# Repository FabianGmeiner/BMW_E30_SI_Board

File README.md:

# About this Project

I'm currently working on a little project for all the early model E30 drivers with SI board trouble from leaky batteries or mechanical damage.

I am reverse engineering the early model SI board, in my case the VDO version (VDO and motometer are interchangeable)

This initial version is a 1:1 copy of the original design. The main microcontroller, the crystal oscillator and the large pin header need to be desoldered and taken over to the new board, but all other components are readily available and stocked parts.

This is mainly to understand the schematics and the workings of the circuit. In a second step I will design my own board with a modern microcontroller and non-volatile storage to work without batteries, with modern and way cheaper components (similar to the board offered by  [ProgRama](https://www.programainc.com/item_detail.aspx?idproduct=177&idcategory=49&sf=)). Also playing with the idea of integrating further functionality, like configurable shift lights on the little indicator board, as all the necessary signals are there anyway.

Warm regards from Germany!

## Current Status

2024/06/24 I received the initial batch of PCBs for testing. This includes the main SI boards as well as the pre-facelift LED board (9 LEDs).

I got all the necessary components from either Mouser or Reichelt (german vendor), but everything is available at Mouser. The [BOM](https://github.com/FabianGmeiner/BMW_E30_SI_Board/blob/main/BOM_SI_Board_Reman.xlsx "BOM_SI_Board_Reman.xlsx") contains all the part descriptions as well as relevant part numbers and the component identification and placement on the second sheet.

The facelift indicator boards (7 LEDs, 3 Bulbs) is based on photographs only, as such I could not yet verify the dimensions apart from measurements from images. 
If anybody has one of those boards laying around and could provide peasurements that would be highly appreciated.

### Testing status

#### Main SI board
**2024/06/24** first board assembled ready for testing.    
**2024/06/30** first functional tests successful. All functions operate as they should, and current consumption is in a nominal range. I am currently building a little pulse generator to test the speed and rpm inputs and test if the oil service lights count down as expected. This will be combined with a long test with the board powered up to check the current consumption and temperatures over longer time. 

| **Test Description**                 | **Current Draw Board** | **Battery Current** | **Further Comments**                                    |
|--------------------------------------|------------------------|---------------------|---------------------------------------------------------|
| Initial Connection, T30 off, T15 off |                        | 9.2 µA              | Battery current measured between BAT_EN jumper          |
| T30 on, T15 off                      | 3.6 mA                 | 5.7 µA              | All lights stay off, battery current reduces.           |
| T30 on, T15 on                       | 145.9 mA               | 5.7 µA              | 5 green LEDs turn on, Inspection light turns on         |
| Activating T50 (starter signal)      |                        |                     | Relay clicks, pad indicator lights up                   |
| Releasing T50 (starter signal)       |                        |                     | Relay clicks, pad indicator turns off, LEDs turn off    |
| Reset Button Pressed                 | 30.4 mA                |                     | INSP light goes out after ~10s, all lights off          |
| T30 on, T15 off                      | 3.6 mA                 |                     | turning ignition off after reset                        |
| T30 on, T15 on                       | 89.4 mA                |                     | ignition back on, 5 green LEDs on, INSP light stays off |
| Activating and releasing T50         | 30.5 mA                |                     | Relay cycles, LEDs turn off. All lights off.            |
| T30 off, T15 off                     |                        | 9.2 µA              |                                                         |
| Battery charging current             |                        | 22.8 mA             | Battery charging with T15 on                            |
| Battery charging cutoff voltage      |                        |                     | Board stops charging at a cell voltage of 1.35 V        |

The overall functionality, the current consumption as well as the charging current and voltage for the NiMh cells is within the expected range. 

#### Indicator board
**2024/06/24** first board assembled. Electrical test ok. Mechanical fitment is off, the connector header needs to be moved up 2.5mm for the board to sit flush with the main PCB.   
**2024/06/27** PCBs are corrected and updated files uploaded. Ordered a new batch of pre-facelift and facelift boards for testing 
**2024/08/22** noticed during assembly that mounding hole of pre-facelift boards is too small. Needs to be enlarged by 0.5mm -> will be corrected in PCB files
**2024/08/23** updated files for bigger mounting hole

## Schematics

Current versions for the main SI board and the LED indicator board are V2 and can be found as .pdf ([2024_06_15_SI_Board_Schematic_V2.pdf](https://github.com/FabianGmeiner/BMW_E30_SI_Board/blob/main/2024_06_15_SI_Board_Schematic_V2.pdf "2024_06_15_SI_Board_Schematic_V2.pdf"), [2024_06_15_Indicator_Schematic_V2.pdf](https://github.com/FabianGmeiner/BMW_E30_SI_Board/blob/main/2024_06_15_Indicator_Schematic_V2.pdf "2024_06_15_Indicator_Schematic_V2.pdf")) or in the respective KiCad projects.

I also added an LED-only-version of the indicator board, replacing the bulbs with white 5mm LEDs and adding current limiting resistors. The resistors will have to be adapted to the LEDs you are using. 
The same goes for a facelift version of the indicator board, with 7 LEDs (one red) and three bulbs.

The schematics also include the pin assignments and routing of the whole instrument cluster (albeit in german), and should also come in as a handy reference for throubelshooting or repairing an original SI board, e.g. with corroded traces.

## Manufacturing files

Exported Gerbers for getting the boards manufactured are located in the respective KiCad project folders for a variety of different board houses. I ordered mine through JLCPCB. 

## Licensing 
LICENSE NOTE: The root license applies to all subfolders NOT containing their own LICENSE file. If a subfolder contains a different LICENSE file this different license applies to all subfolders below this LICENSE file.

I encourage everyone to get the boards manufactured yourself as the components are cheaply available and its a cool project to keep our old cars running nicely.
If you want to sell any hardware of this project yourself i would kindly ask you to get in contact with me.

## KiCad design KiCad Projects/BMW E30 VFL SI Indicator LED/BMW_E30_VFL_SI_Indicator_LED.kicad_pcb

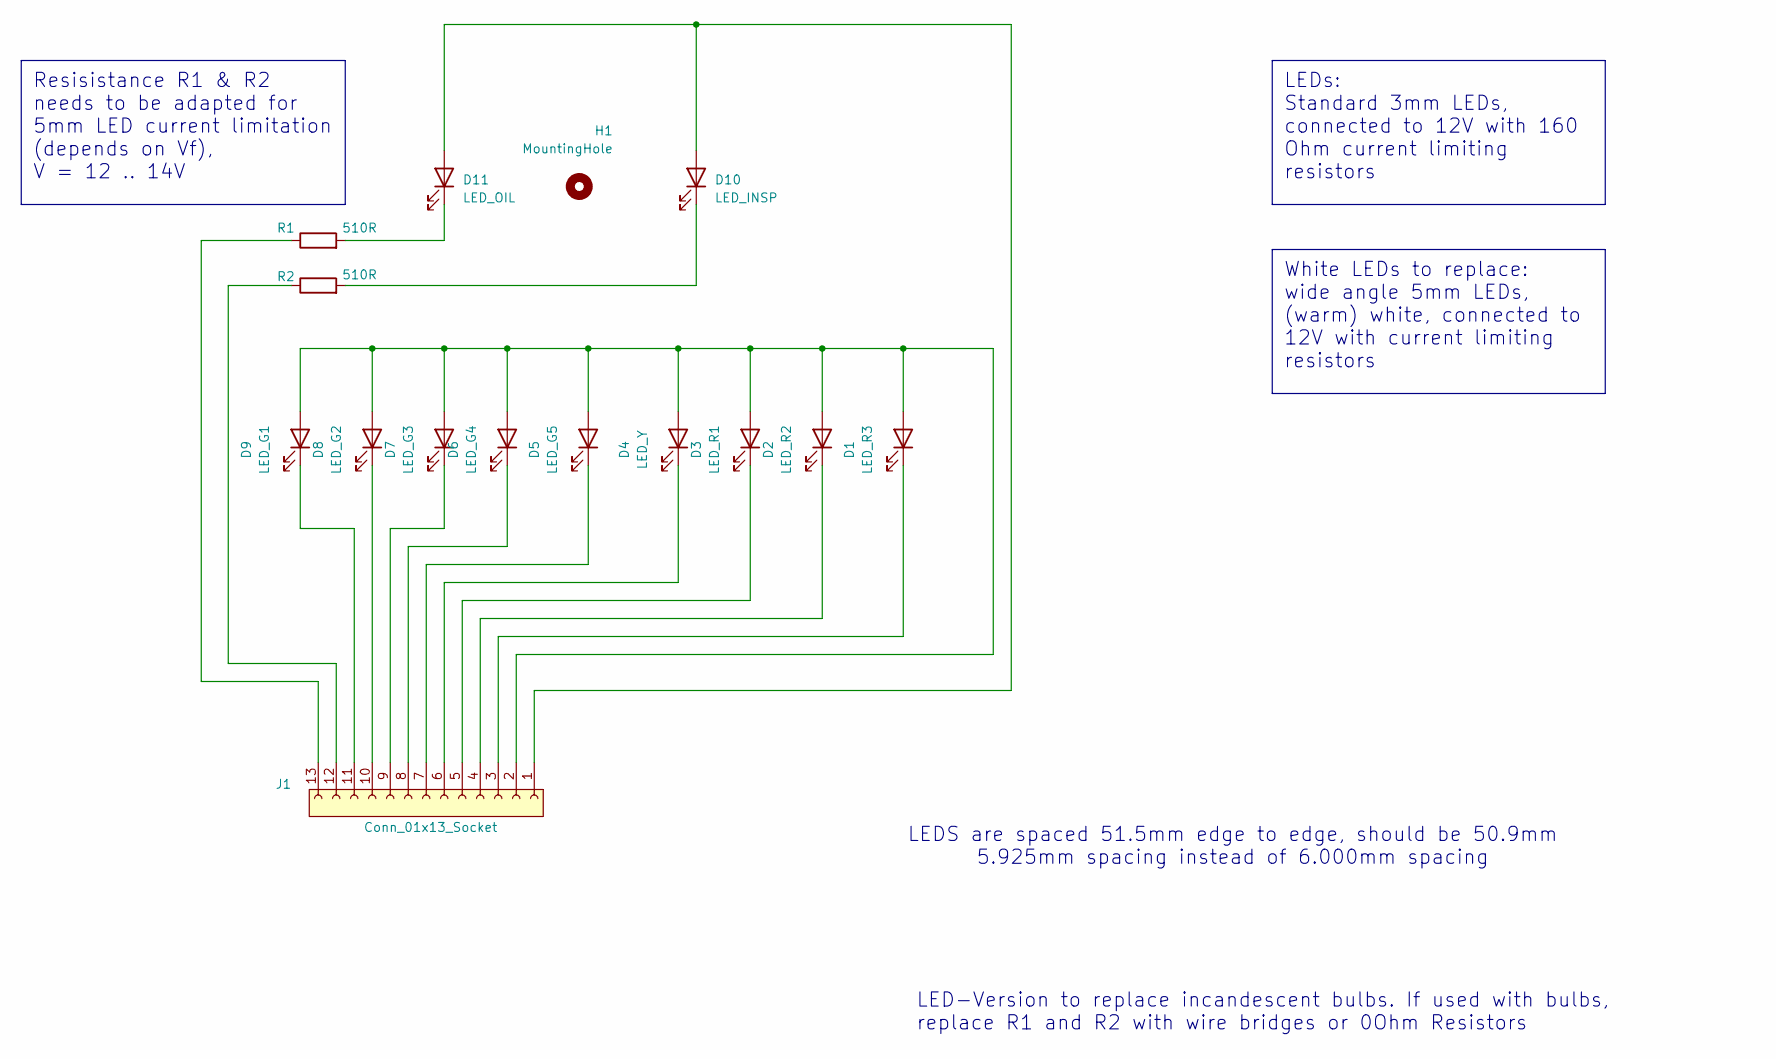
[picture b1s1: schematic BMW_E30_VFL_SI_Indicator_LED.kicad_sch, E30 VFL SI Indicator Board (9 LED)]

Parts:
D1: LED_R3; LED_D3.0mm
D2: LED_R2; LED_D3.0mm
D3: LED_R1; LED_D3.0mm
D4: LED_Y; LED_D3.0mm
D5: LED_G5; LED_D3.0mm
D6: LED_G4; LED_D3.0mm
D7: LED_G3; LED_D3.0mm
D8: LED_G2; LED_D3.0mm
D9: LED_G1; LED_D3.0mm
D10: LED_INSP; LED_Rectangular_W5.0mm_H2.0mm_Horizontal_O6.35mm_Z1.0mm
D11: LED_OIL; LED_Rectangular_W5.0mm_H2.0mm_Horizontal_O6.35mm_Z3.0mm
H1: MountingHole; MountingHole_6.5mm
J1: Conn_01x13_Socket; PinSocket_1x13_P2.54mm_Horizontal
R1, R2: 510R; R_Axial_DIN0207_L6.3mm_D2.5mm_P7.62mm_Horizontal

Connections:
unnamed: D1.2 (A), D2.2 (A), D3.2 (A), D4.2 (A), D5.2 (A), D6.2 (A), D7.2 (A), D8.2 (A), D9.2 (A), J1.2 (GND_LED)
unnamed: D1.1 (K), J1.3 (LED_R3)
unnamed: D2.1 (K), J1.4 (LED_R2)
unnamed: D3.1 (K), J1.5 (LED_R1)
unnamed: D4.1 (K), J1.6 (LED_Y)
unnamed: D5.1 (K), J1.7 (LED_G5)
unnamed: D6.1 (K), J1.8 (LED_G4)
unnamed: D7.1 (K), J1.9 (LED_G3)
unnamed: D8.1 (K), J1.10 (LED_G2)
unnamed: D9.1 (K), J1.11 (LED_G1)
unnamed: D10.2 (A), D11.2 (A), J1.1 (GND_BULB)
unnamed: D10.1 (K), R2.2
unnamed: D11.1 (K), R1.2
unnamed: J1.12 (BULB_INSPECTION), R2.1
unnamed: J1.13 (BULB_OILSERVICE), R1.1

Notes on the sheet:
White LEDs to replace: wide angle 5mm LEDs, (warm) white, connected to 12V with current limiting resistors
LEDs: Standard 3mm LEDs, connected to 12V with 160 Ohm current limiting resistors
Resisistance R1 & R2 needs to be adapted for 5mm LED current limitation (depends on Vf), V = 12 .. 14V
LEDS are spaced 51.5mm edge to edge, should be 50.9mm 5.925mm spacing instead of 6.000mm spacing
LED-Version to replace incandescent bulbs. If used with bulbs, replace R1 and R2 with wire bridges or 0Ohm Resistors

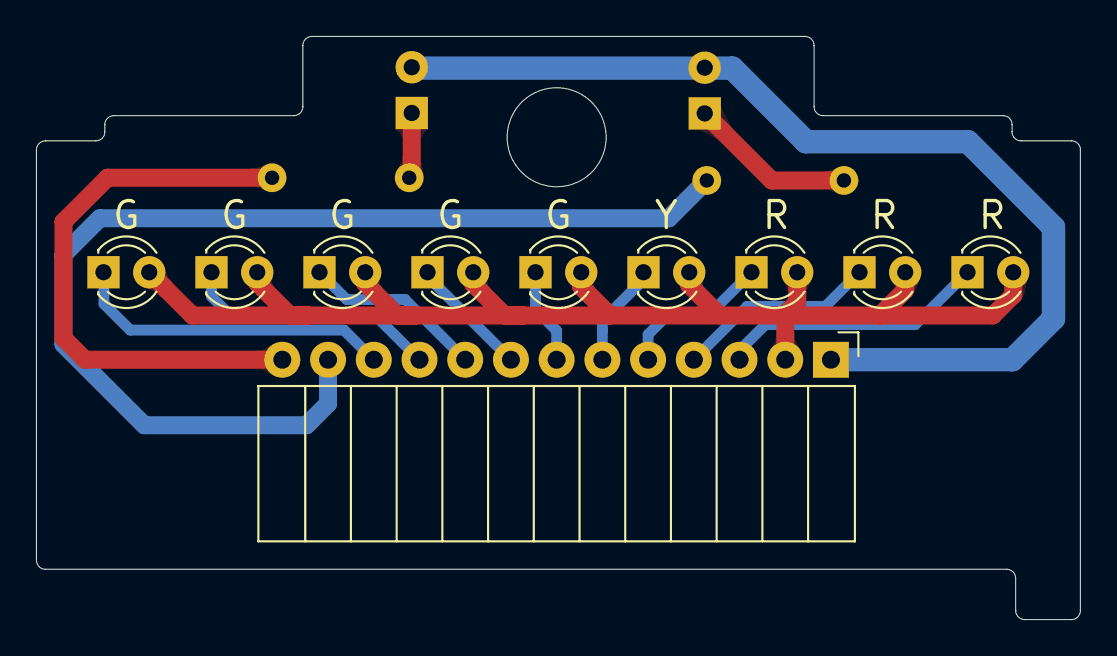
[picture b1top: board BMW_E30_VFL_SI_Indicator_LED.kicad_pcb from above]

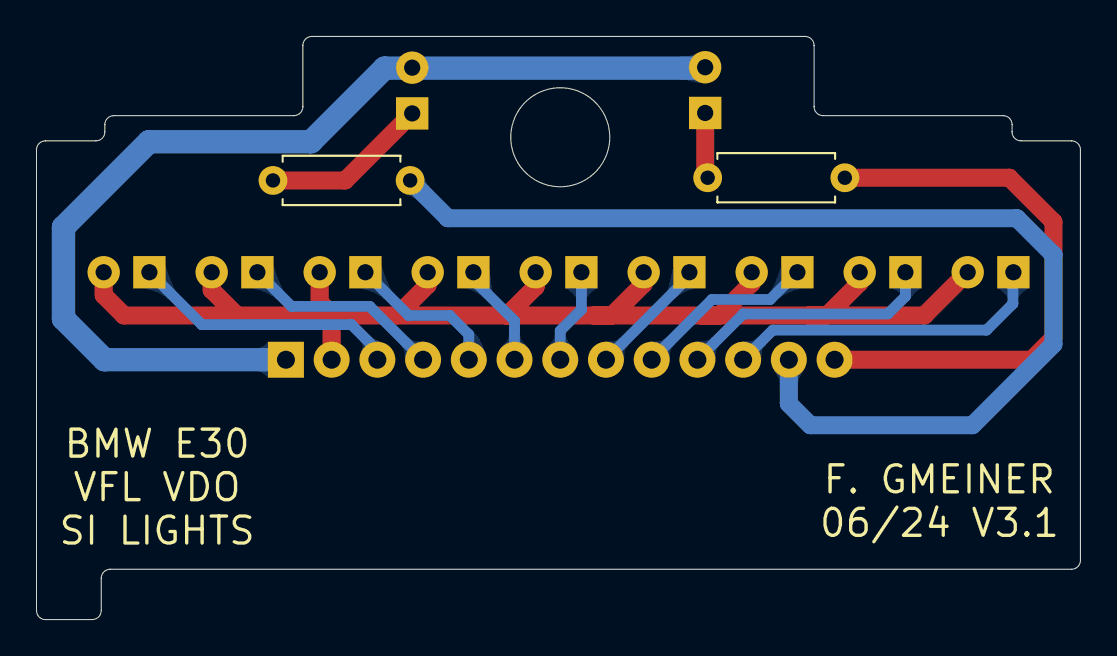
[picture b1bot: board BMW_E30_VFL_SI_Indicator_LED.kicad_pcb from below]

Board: 2 copper layers, 58.0 x 32.4 mm, 15 parts (2 on the bottom side), 15 nets.

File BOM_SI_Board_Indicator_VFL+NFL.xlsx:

|  |  | BMW E30 VFL Si-Board Indicator Bill of Materials
 |  |  |  |  |  |  |  |  | SUMME Reichelt
 |  |  |  |  |  |  |  |  | 0.9900000000000001
 | Sum of Qty: | 15
Item # | *Designator | *Qty | Manufacturer | Description / Value | *Package/Footprint | Type | Reichelt Nr. | Reichelt Unit Price | Reichelt Total Price
1 | PCB | 1 |  | Manufacturing Files on Github |  | Custom |  |  | 0
2 | LED Holder | 1 |  | 3D Files on Github |  | Custom |  |  | 0
3 | D1-D3 | 3 |  | Red LED, 3mm, 50mA | 3mm THT |  | LED 3MM RT | 7.0000000000000007E-2 | 0.21000000000000002
4 | D4 | 1 |  | Yellow LED, 3mm, 50mA | 3mm THT |  | LED 3MM GE | 7.0000000000000007E-2 | 7.0000000000000007E-2
5 | D5-D9 | 5 |  | Green LED, 3mm, 50mA | 3mm THT |  | LED 3MM GN | 7.0000000000000007E-2 | 0.35000000000000003
6 | D10, D11 | 2 |  | White LED, rectangular 2x5mm, 250mcd, 20mA | rectangular 2x5mm THT |  | 2534W2D-KHA-A | 0.11 | 0.22
7 | R1, R2 | 2 |  | 510 Ohms 5% 1/4W | THT |  | METALL 510 | 7.0000000000000007E-2 | 0.14000000000000001

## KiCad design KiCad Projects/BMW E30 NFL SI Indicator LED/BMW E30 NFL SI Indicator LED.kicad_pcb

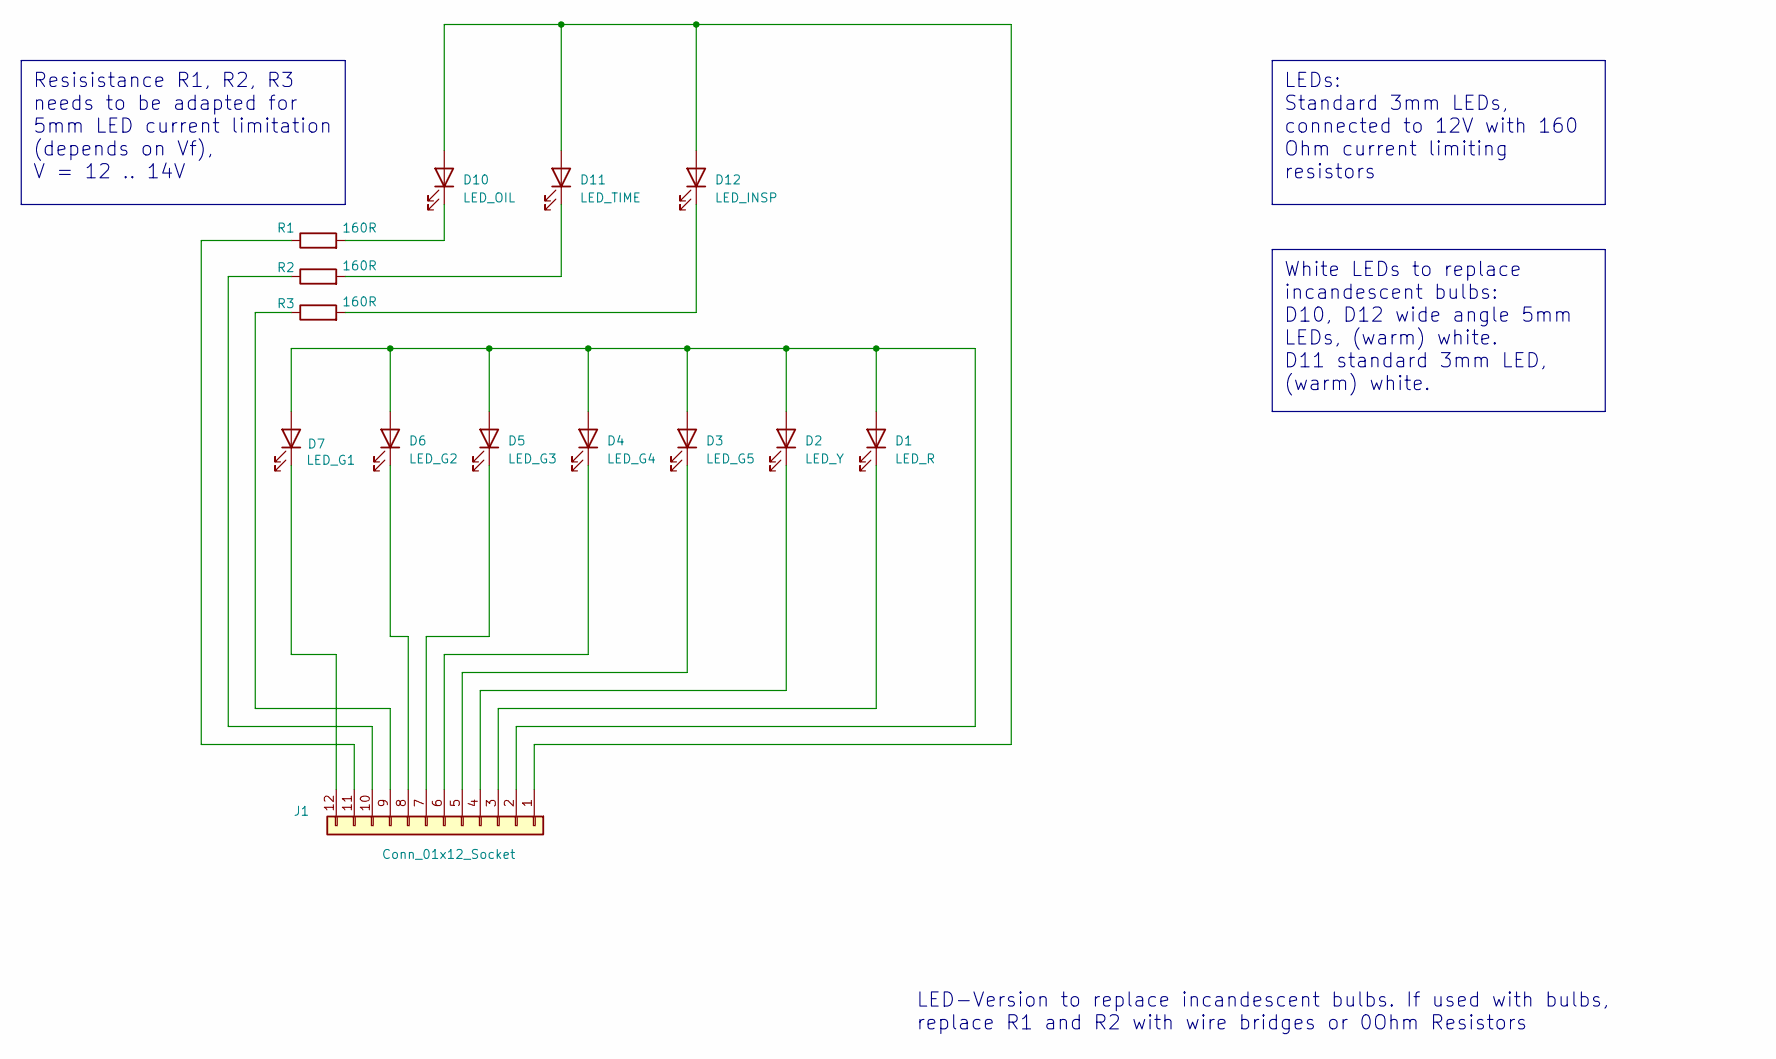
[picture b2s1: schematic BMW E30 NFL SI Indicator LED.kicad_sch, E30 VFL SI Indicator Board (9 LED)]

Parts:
D1: LED_R; LED_D3.0mm
D2: LED_Y; LED_D3.0mm
D3: LED_G5; LED_D3.0mm
D4: LED_G4; LED_D3.0mm
D5: LED_G3; LED_D3.0mm
D6: LED_G2; LED_D3.0mm
D7: LED_G1; LED_D3.0mm
D10: LED_OIL; LED_Rectangular_W5.0mm_H2.0mm_Horizontal_O3.81mm_Z1.0mm
D11: LED_TIME; LED_D3.0mm_Clear
D12: LED_INSP; LED_Rectangular_W5.0mm_H2.0mm_Horizontal_O3.81mm_Z1.0mm
J1: Conn_01x12_Socket; PinSocket_1x12_P2.54mm_Horizontal
R1, R2, R3: 160R; R_Axial_DIN0207_L6.3mm_D2.5mm_P7.62mm_Horizontal

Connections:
unnamed: D1.2 (A), D2.2 (A), D3.2 (A), D4.2 (A), D5.2 (A), D6.2 (A), D7.2 (A), J1.2 (T15_LEDS)
unnamed: D1.1 (K), J1.3 (LED_R)
unnamed: D2.1 (K), J1.4 (LED_Y)
unnamed: D3.1 (K), J1.5 (LED_G5)
unnamed: D4.1 (K), J1.6 (LED_G4)
unnamed: D5.1 (K), J1.7 (LED_G3)
unnamed: D6.1 (K), J1.8 (LED_G2)
unnamed: D7.1 (K), J1.12 (LED_G1)
unnamed: D10.2 (A), D11.2 (A), D12.2 (A), J1.1 (T15_BULBS)
unnamed: D10.1 (K), R1.2
unnamed: D11.1 (K), R2.2
unnamed: D12.1 (K), R3.2
unnamed: J1.9 (BULB_INSP), R3.1
unnamed: J1.11 (BULB_OIL), R1.1
unnamed: J1.10 (BULB_TIME), R2.1

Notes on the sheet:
White LEDs to replace incandescent bulbs: D10, D12 wide angle 5mm LEDs, (warm) white. D11 standard 3mm LED, (warm) white.
LEDs: Standard 3mm LEDs, connected to 12V with 160 Ohm current limiting resistors
Resisistance R1, R2, R3 needs to be adapted for 5mm LED current limitation (depends on Vf), V = 12 .. 14V
LED-Version to replace incandescent bulbs. If used with bulbs, replace R1 and R2 with wire bridges or 0Ohm Resistors

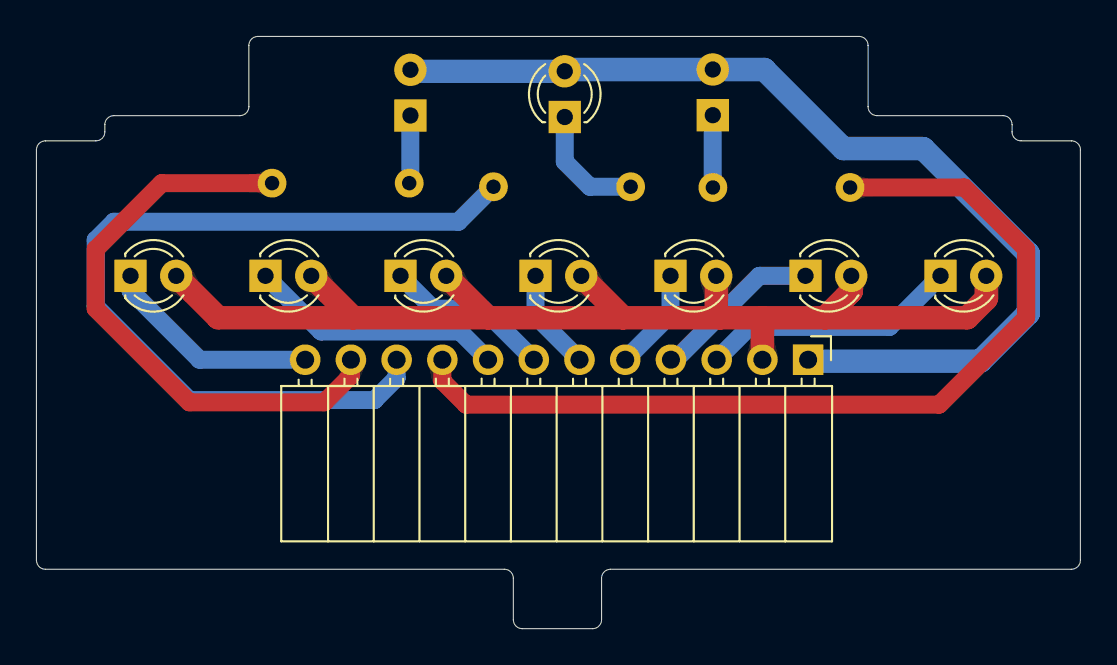
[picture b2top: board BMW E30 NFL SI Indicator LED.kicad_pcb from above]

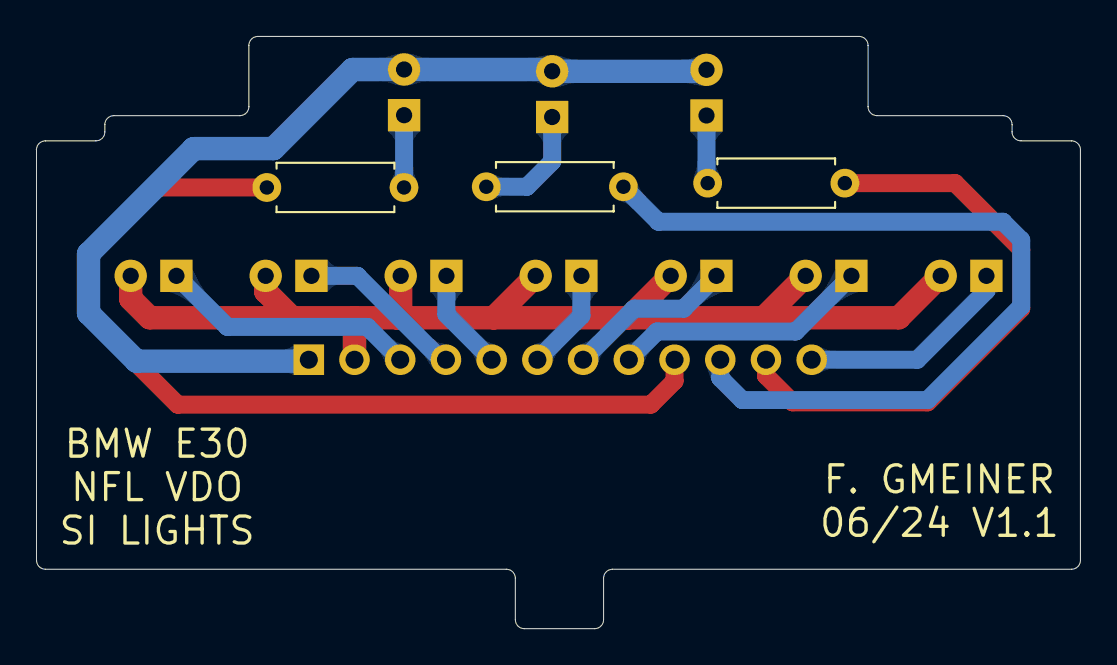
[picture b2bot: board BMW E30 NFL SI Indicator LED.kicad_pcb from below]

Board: 2 copper layers, 58.0 x 32.9 mm, 14 parts (3 on the bottom side), 15 nets.

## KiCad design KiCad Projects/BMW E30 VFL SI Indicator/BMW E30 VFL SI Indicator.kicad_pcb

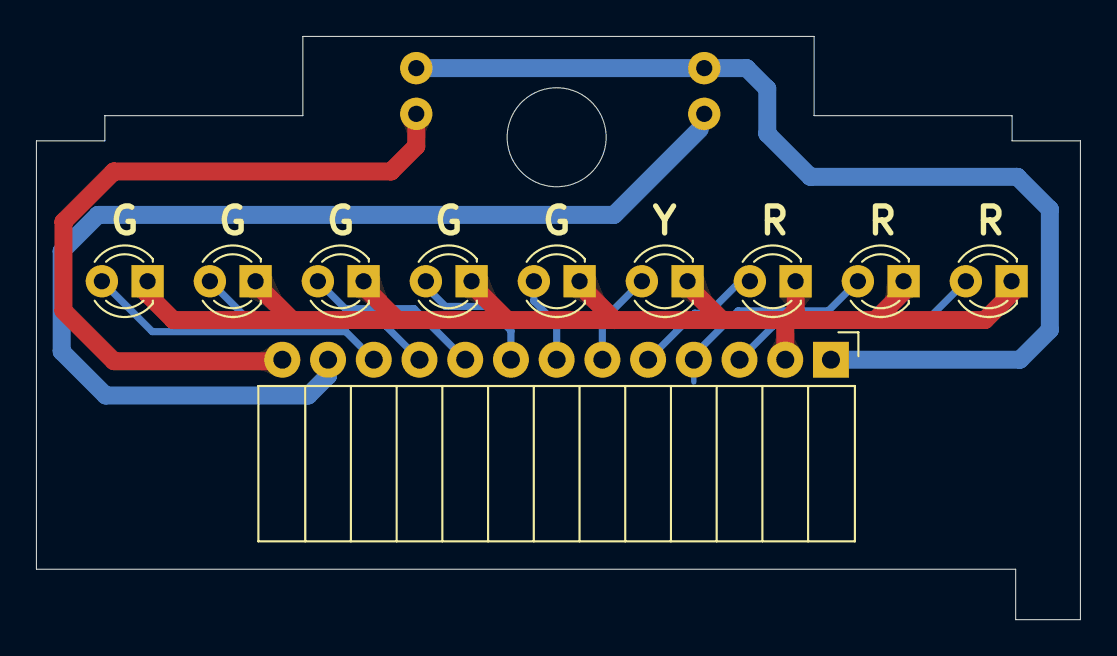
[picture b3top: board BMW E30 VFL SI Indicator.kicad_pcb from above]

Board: 2 copper layers, 58.0 x 32.4 mm, 13 parts (0 on the bottom side), 13 nets.

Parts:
D1: LED_R3; LED_D3.0mm
D2: LED_R2; LED_D3.0mm
D3: LED_R1; LED_D3.0mm
D4: LED_Y; LED_D3.0mm
D5: LED_G5; LED_D3.0mm
D6: LED_G4; LED_D3.0mm
D7: LED_G3; LED_D3.0mm
D8: LED_G2; LED_D3.0mm
D9: LED_G1; LED_D3.0mm
H1: MountingHole; MountingHole_5.5mm
J1: Conn_01x13_Socket; PinSocket_1x13_P2.54mm_Horizontal
LA1, LA2: Lamp; Lamp_D4.0mm_Horizontal_O3.81mm_Z2.0mm

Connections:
unnamed: D1.2 (A), J1.3 (LED_R3)
unnamed: D1.1 (K), D2.1 (K), D3.1 (K), D4.1 (K), D5.1 (K), D6.1 (K), D7.1 (K), D8.1 (K), D9.1 (K), J1.2 (GND_LED)
unnamed: D2.2 (A), J1.4 (LED_R2)
unnamed: D3.2 (A), J1.5 (LED_R1)
unnamed: D4.2 (A), J1.6 (LED_Y)
unnamed: D5.2 (A), J1.7 (LED_G5)
unnamed: D6.2 (A), J1.8 (LED_G4)
unnamed: D7.2 (A), J1.9 (LED_G3)
unnamed: D8.2 (A), J1.10 (LED_G2)
unnamed: D9.2 (A), J1.11 (LED_G1)
unnamed: J1.12 (BULB_INSPECTION), LA2.1 (-)
unnamed: J1.13 (BULB_OILSERVICE), LA1.2 (+)
unnamed: J1.1 (GND_BULB), LA1.1 (-), LA2.2 (+)
